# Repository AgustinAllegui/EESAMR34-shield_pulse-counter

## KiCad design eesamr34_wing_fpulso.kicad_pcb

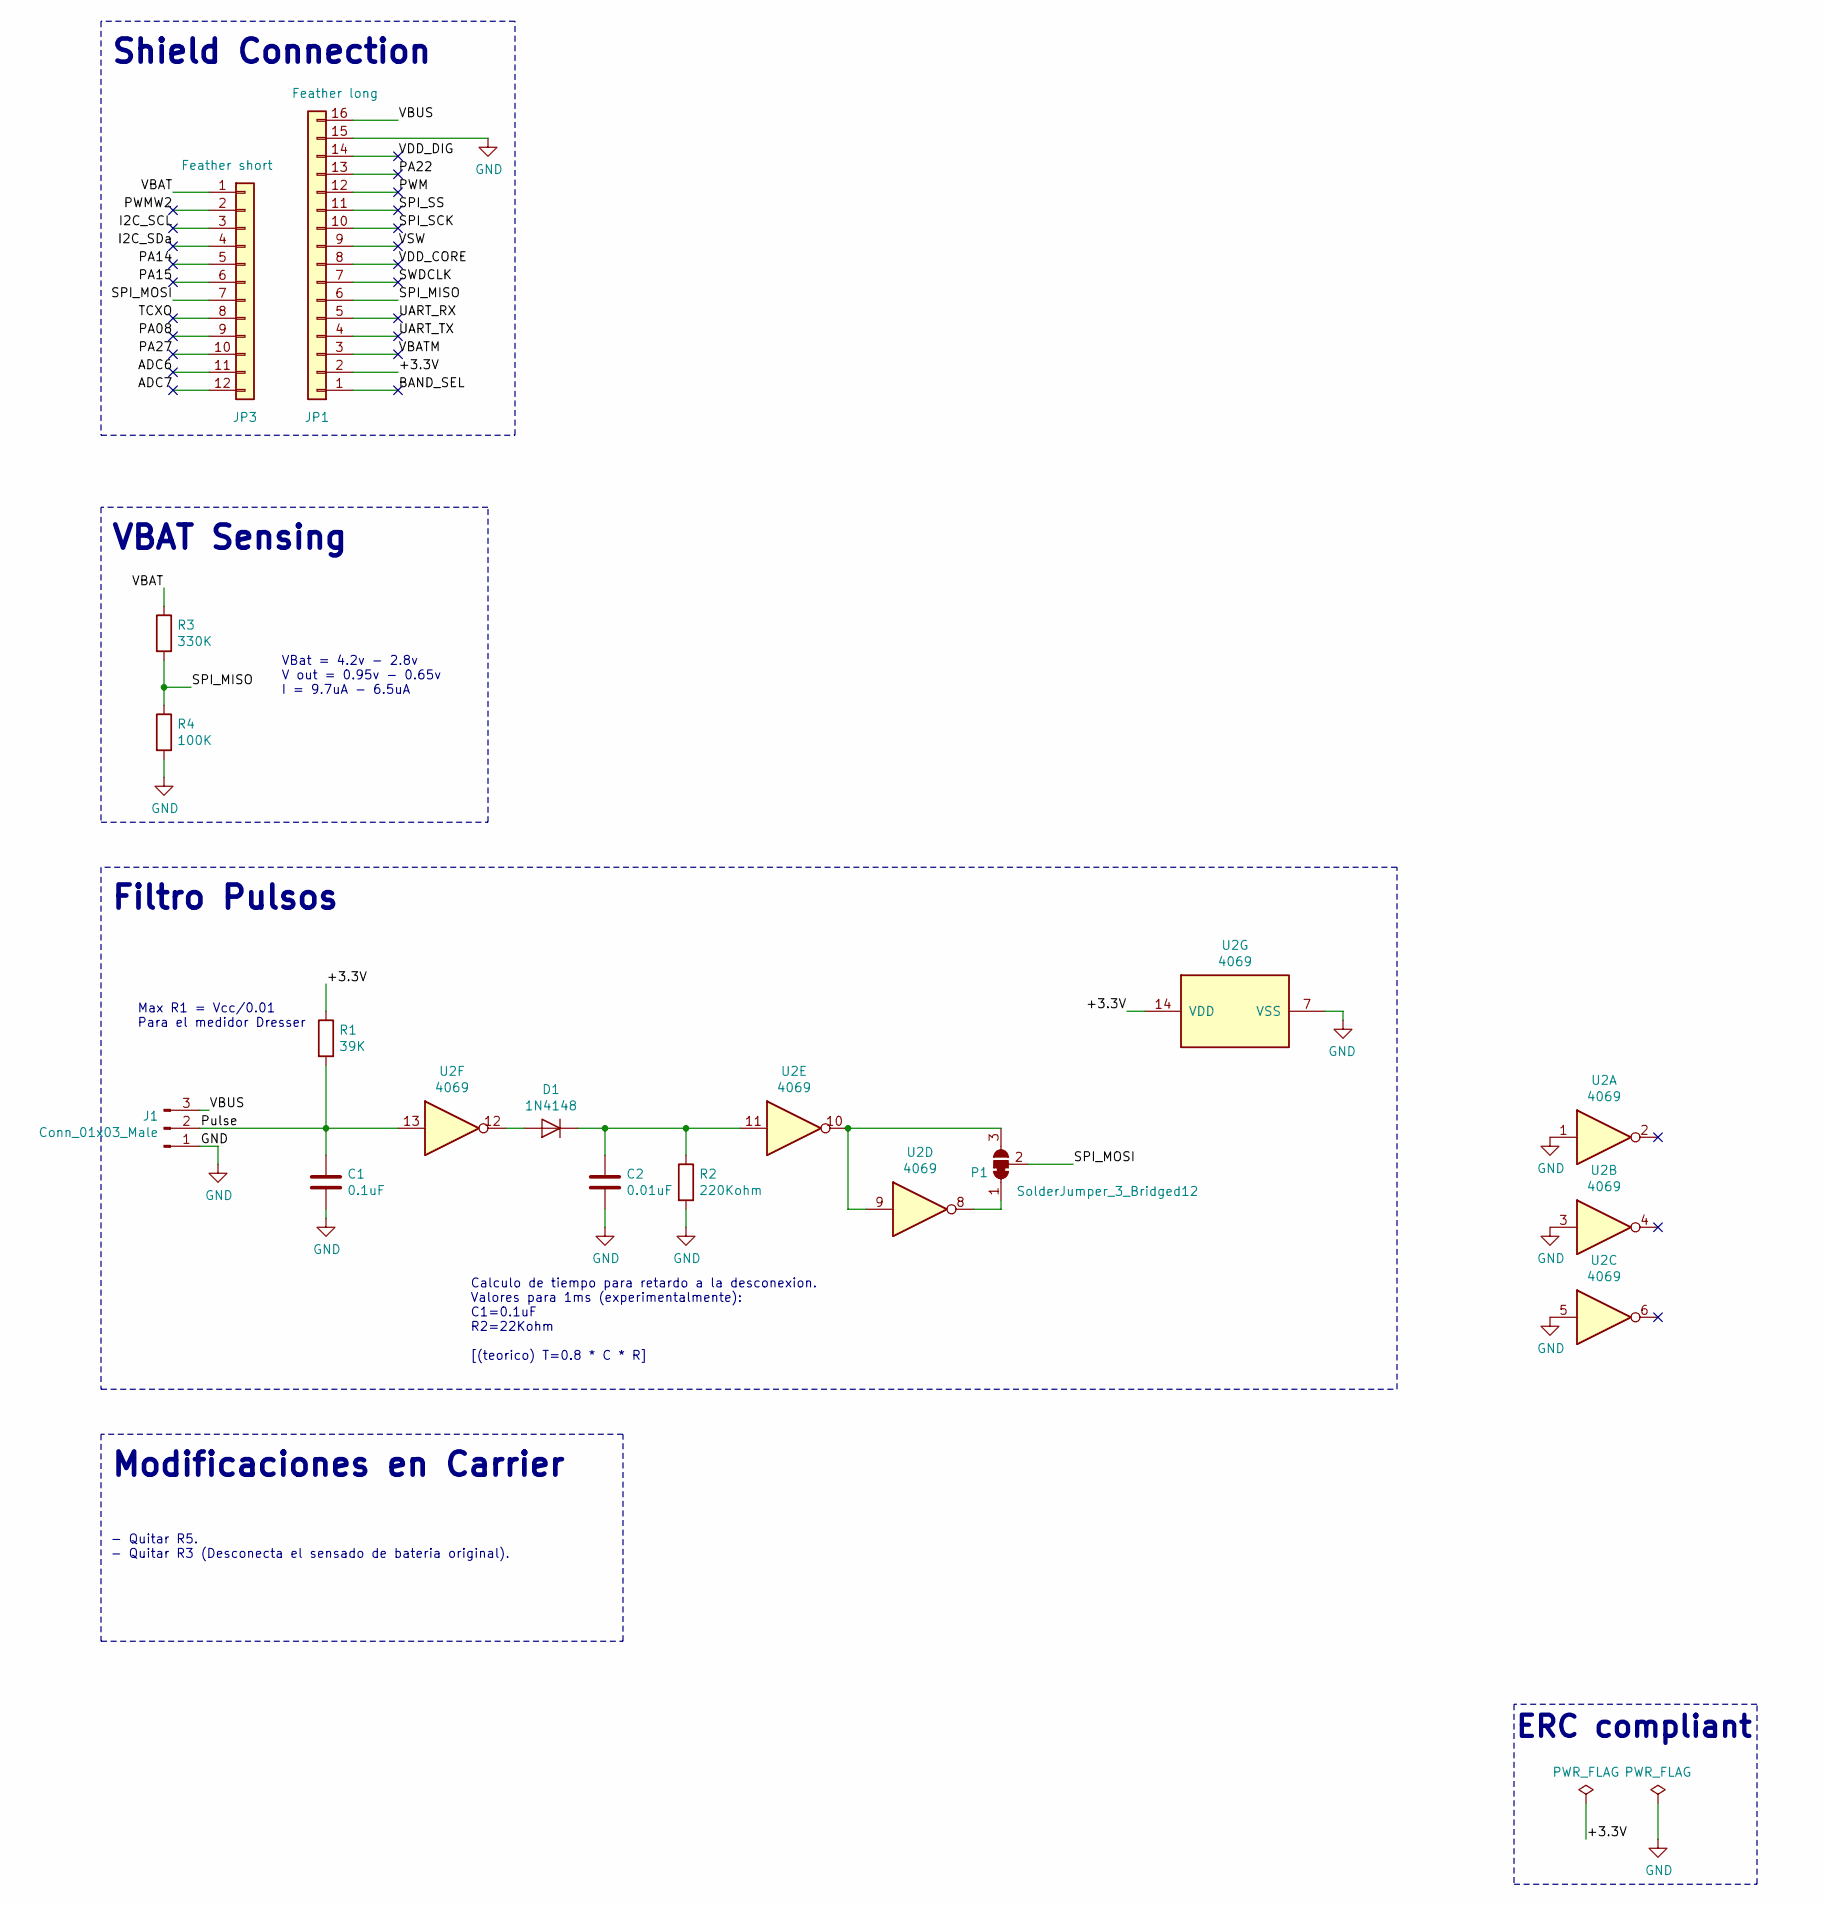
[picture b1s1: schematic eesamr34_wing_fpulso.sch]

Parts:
C1: 0.1uF; C_Disc_D5.0mm_W2.5mm_P2.50mm
C2: 0.01uF; C_Disc_D5.0mm_W2.5mm_P2.50mm
D1: 1N4148; D_DO-35_SOD27_P7.62mm_Horizontal
J1: Conn_01x03_Male; TerminalBlock_bornier-3_P5.08mm
JP1: Feather long; PinSocket_1x16_P2.54mm_Vertical
JP3: Feather short; PinSocket_1x12_P2.54mm_Vertical
P1: SolderJumper_3_Bridged12; SolderJumper-3_P1.3mm_Bridged12_Pad1.0x1.5mm
R1: 39K; R_Axial_DIN0207_L6.3mm_D2.5mm_P10.16mm_Horizontal
R2: 220Kohm; R_Axial_DIN0207_L6.3mm_D2.5mm_P10.16mm_Horizontal
R3: 330K; R_Axial_DIN0207_L6.3mm_D2.5mm_P10.16mm_Horizontal
R4: 100K; R_Axial_DIN0207_L6.3mm_D2.5mm_P10.16mm_Horizontal
U2: 4069; DIP-14_W7.62mm

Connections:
/+3.3V: JP1.2, R1.1, U2.14 (VDD)
/ADC6: JP3.11
/ADC7: JP3.12
/BAND_SEL: JP1.1
/I2C_SCL: JP3.3
/I2C_SDa: JP3.4
/PA08: JP3.9
/PA14: JP3.5
/PA15: JP3.6
/PA22: JP1.13
/PA27: JP3.10
/PWM: JP1.12
/PWMW2: JP3.2
/Pulse: C1.1, J1.2, R1.2, U2.13
/SPI_MISO: JP1.6, R3.2, R4.1
/SPI_MOSI: JP3.7, P1.2 (C)
/SPI_SCK: JP1.10
/SPI_SS: JP1.11
/SWDCLK: JP1.7
/TCXO: JP3.8
/UART_RX: JP1.5
/UART_TX: JP1.4
/VBAT: JP3.1, R3.1
/VBATM: JP1.3
/VBUS: J1.3, JP1.16
/VDD_CORE: JP1.8
/VDD_DIG: JP1.14
/VSW: JP1.9
GND: C1.2, C2.2, J1.1, JP1.15, R2.2, R4.2, U2.1, U2.3, U2.5, U2.7 (VSS)
unnamed: C2.1, D1.1 (K), R2.1, U2.11
unnamed: D1.2 (A), U2.12
unnamed: P1.1 (A), U2.8
unnamed: P1.3 (B), U2.9, U2.10

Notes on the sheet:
Calculo de tiempo para retardo a la desconexion. Valores para 1ms (experimentalmente): C1=0.1uF R2=22Kohm [(teorico) T=0.8 * C * R]
Max R1 = Vcc/0.01 Para el medidor Dresser
Filtro Pulsos
Shield Connection
ERC compliant
- Quitar R5. - Quitar R3 (Desconecta el sensado de bateria original).
Modificaciones en Carrier
VBat = 4.2v - 2.8v V out = 0.95v - 0.65v I = 9.7uA - 6.5uA
VBAT Sensing

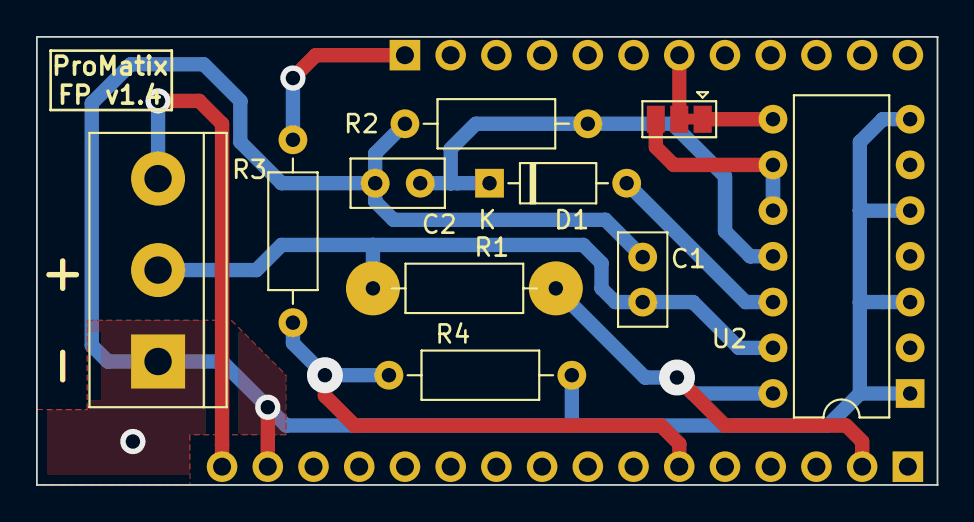
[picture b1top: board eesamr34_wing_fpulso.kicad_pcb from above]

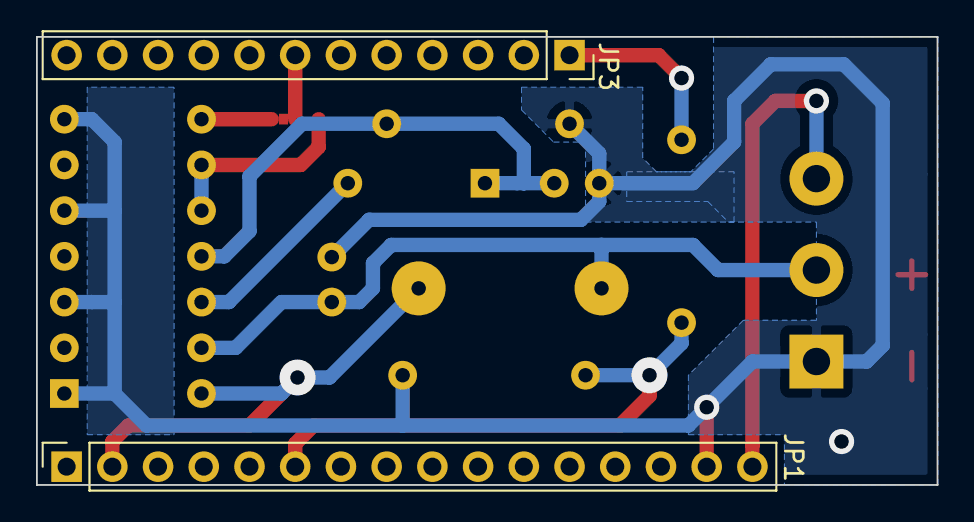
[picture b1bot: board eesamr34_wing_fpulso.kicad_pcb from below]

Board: 2 copper layers, 50.0 x 24.9 mm, 12 parts (2 on the bottom side), 11 nets.

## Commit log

2020-09-14 Second commit
2020-09-17 Added ibom, gerbers
2020-09-21 Resize VIAS
2020-09-24 Changed to PA08
2020-10-26 Agregados leds, sensado y conexion de bateria
2020-10-28 entradas no usadas a 0
2020-11-03 cambios menores
2020-11-03 Reducido consumo de pullup y filtro
2020-11-04 quitado vbat to vcc y actualizado PCB
2021-02-11 Tercer borne permite alimentar el nodo usando 5v
